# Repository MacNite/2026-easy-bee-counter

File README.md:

# Bee Counter Redesign — Full Specification
### Single PCB + 3D Printed Housing, reported over BLE to HiveHub

A redesign of the [2019-easy-bee-counter](https://github.com/hydronics2/2019-easy-bee-counter)
by hydronics2: 24 entrance gates, 48 reflective IR sensors read through I²C
port expanders, and an always-on ESP32-C6 doing the counting and reporting
totals over BLE.

> **Status:** the PCB (`PCB_files/easy-bee-counter-2026.kicad_*`) and the
> ESP32-C6 firmware (`Firmware/`) are implemented. The 3D-printed housing
> (Section 5) is the remaining mechanical work.

---

## 1. System Overview

The **ESP32-C6 mini** runs always-on as a dedicated bee counter and advertises
as a connectable BLE peripheral. A HiveHub wakes roughly every 10 minutes,
connects, reads one JSON characteristic of lifetime totals and disconnects,
combining the counts with weight/timestamp data before logging and transmitting.

```
[HiveHub ESP32] ←——— BLE/GATT ———→ [ESP32-C6 mini]
  wakes every ~10 min                always-on, ~15 mA
  RTC, SD, WiFi, scale               bee counting, 3× MCP23017 (I²C)
```

The counter's own I²C bus (`Wire`, silk D4 = GPIO22 SDA / silk D5 = GPIO23 SCL) is used only to reach
the 3× MCP23017 port expanders.

> **The wired HiveScale link is gone.** Earlier revisions ran the C6's second
> I²C controller as a permanent slave at 0x30, serving a register map to a
> HiveScale polling over J1 — and the firmware for it has been removed, because
> HiveHub reads counters over BLE only and dropped its wired client. Sections
> below still describe the J1 connector and its cable, since both are physically
> on the PCB; no firmware brings that bus up, so populating them is optional.

---

## 2. Complete Bill of Materials

### 2.1 Microcontroller

| # | Component | Qty | Notes |
|---|-----------|-----|-------|
| 1 | Seeed XIAO ESP32C6 (Seeed 113991054) | 1 | Always-on bee counter MCU. ~15 mA active, 3.3 V logic, USB-C. Two hardware I²C controllers. **Silk D0..D10 ≠ GPIO numbers** — see `Firmware/include/pins.h` |

### 2.2 I/O Expansion (replaces all 6× 74HC165)

| # | Component | Qty | Notes |
|---|-----------|-----|-------|
| 2 | MCP23017-E/SP (DIP-28) | 3 | 16 inputs each = 48 total. I²C addresses 0x20, 0x21, 0x22 (on bus 0) |

### 2.3 IR Sensors

| # | Component | Qty | Notes |
|---|-----------|-----|-------|
| 3 | QRE1113 or ITR8307 reflectance sensor | 48 | 2 per gate × 24 gates. ITR8307 from LCSC is cheaper (~€0.13 each) |

### 2.4 MOSFETs (IR LED switching)

| # | Component | Qty | Notes |
|---|-----------|-----|-------|
| 4 | IRLB8721PbF N-channel MOSFET (TO-220) | 3 | 3.3 V gate-safe. One per MCP23017: Q1 = LED_BANK_1 (gates 00..07), Q2 = LED_BANK_2 (gates 10..17), Q3 = LED_BANK_3 (gates 20..27). Individually switchable at runtime — see [Power Budget](#6-power-budget) |

### 2.5 Resistors

| # | Component | Qty | Notes |
|---|-----------|-----|-------|
| 5 | 22 Ω bussed SIP resistor (9-pin, 8R) | 3 | IR LED current limiting (2 LEDs in series per gate) |
| 6 | 100 kΩ bussed SIP resistor (9-pin, 8R) | 6 | Sensor pull-up resistors (1 per MCP23017 input, to +3.3 V) |
| 7 | 10 kΩ resistor (through-hole) | 6 | MOSFET gate pull-downs (3×), MCP23017 RESET pull-ups (3×) |
| 8 | 4.7 kΩ resistor (through-hole) | 2 | Bus 0 I²C pull-ups (SDA + SCL to 3.3 V), R4/R5 |

> J1 (the retired HiveScale link) does **not** need on-board pull-ups — those were
> provided by the HiveScale-side I²C network.

### 2.6 Capacitors

| # | Component | Qty | Notes |
|---|-----------|-----|-------|
| 9 | 100 nF ceramic capacitor (through-hole) | 6 | Decoupling, 1 per MCP23017 VDD pin + 3 spare |
| 10 | 10 µF electrolytic capacitor | 1 | Bulk decoupling on 3.3 V rail |

### 2.7 Connectors

| # | Component | Qty | Notes |
|---|-----------|-----|-------|
| 11 | 4-pin JST-PH or screw terminal (I²C bus 1 + GND + 3.3 V) | 1 | Connection cable to HiveScale (J1) |
| 12 | 2-pin screw terminal | 1 | 3.3 V power input from HiveScale |
| 13 | USB-C connector (on C6 mini board) | — | For firmware flashing / serial only |

### 2.8 PCB & Housing

| # | Component | Qty | Notes |
|---|-----------|-----|-------|
| 14 | Custom PCB (single board, black substrate) | 1 | Designed in KiCad (`PCB_files/`). Order black. See Section 4 |
| 15 | 3D printed top baffle / housing | 1 | Carbon-filled PETG or ASA. See Section 5 |
| 16 | M2×6 screws | 8 | PCB to housing standoffs |
| 17 | M2 brass heat-set inserts | 8 | Into 3D printed housing |

---

## 3. Wiring & Connection Map

### 3.1 I²C Buses

This board uses **two separate I²C buses**, one per controller:

**Bus 0 (`Wire`) — MCP23017 master bus.** Silk D4 = GPIO22 = SDA, silk D5 = GPIO23 = SCL. On-board
4.7 kΩ pull-ups (R4/R5) to 3.3 V.

```
XIAO D4 = GPIO22 (SDA) ——+——————+——————+——— 4.7 kΩ ——→ 3.3 V
                        |      |      |
                      MCP1   MCP2   MCP3
                      0x20   0x21   0x22

XIAO D5 = GPIO23 (SCL) ——+——————+——————+——— 4.7 kΩ ——→ 3.3 V
```

**J1 (silk D2 / D3 = GPIO2 / GPIO21) — the retired HiveScale slave bus.** The pads and traces
are on the board, and pull-ups were supplied by the HiveScale side. **No current
firmware brings this controller up**, so the pins stay inputs and populating J1
is optional — see the note in Section 1.

> **Note on the schematic net names:** the schematic labels the master bus nets
> "/SDA" and "/SDC" (a typo for SCL), and the LED-bank nets "/GPIO4" / "/GPIO5"
> / "/GPIO6". Those are just net *names* — physically the LED banks are driven
> from silk D8 = GPIO19, D9 = GPIO20 and D10 = GPIO18. U5 is a Seeed XIAO ESP32C6, whose silk
> numbers are **not** its GPIO numbers; see `Firmware/include/pins.h` for the
> authoritative map.

### 3.2 MCP23017 Wiring (repeat for each of the 3 chips, all on bus 0)

| MCP23017 Pin | Connection | Notes |
|---|---|---|
| 9 (VDD) | 3.3 V | Add 100 nF ceramic cap to GND nearby |
| 10 (VSS) | GND | |
| 12 (SCL) | Bus 0 SCL (silk D5 = GPIO23) | |
| 13 (SDA) | Bus 0 SDA (silk D4 = GPIO22) | |
| 15 (A0) | GND / 3.3 V | Address bit 0 (see table below) |
| 16 (A1) | GND / 3.3 V | Address bit 1 |
| 17 (A2) | GND / 3.3 V | Address bit 2 |
| 18 (RESET) | 3.3 V via 10 kΩ | Tie high; no active reset needed |
| 21–28 (GPA0–7) | IR sensor outputs (inner sensors) | 8 sensors per chip |
| 1–8 (GPB0–7) | IR sensor outputs (outer sensors) | 8 sensors per chip |

**Address configuration:**

| Chip | I²C Address | A2 | A1 | A0 | Gates |
|------|-------------|----|----|----|----|
| MCP1 (U2) | 0x20 | GND | GND | GND | 00–07 |
| MCP2 (U3) | 0x21 | GND | GND | 3.3 V | 10–17 |
| MCP3 (U4) | 0x22 | GND | 3.3 V | GND | 20–27 |

> Gate tags have gaps (08, 09, 18, 19, 28, 29 are skipped) to keep the
> per-chip pin→gate map clean; there are 24 physical gates indexed 0..23
> internally.

### 3.3 IR Sensor Wiring (per sensor pair, 24× repeated)

Each gate has 2 sensors — one "inner" (towards hive), one "outer" (towards field).

```
QRE1113 pin 1 (Anode / LED+)   ——→ LED string common (+ / 3.3 V via 22 Ω)
QRE1113 pin 2 (Cathode / LED-) ——→ MOSFET Drain (bank rail)
QRE1113 pin 3 (Collector)      ——→ MCP23017 GPIO input pin + 100 kΩ pull-up to 3.3 V
QRE1113 pin 4 (Emitter)        ——→ GND
```

Logical convention in firmware: **sensor reads LOW = beam reflected/blocked
(bee in beam); HIGH = clear or LEDs off.**

### 3.4 MOSFET Wiring (IRLB8721PbF, 3× identical — one per MCP23017)

| IRLB8721 Pin | Connection |
|---|---|
| Gate (pin 1) | Bank enable GPIO from the table below, + 10 kΩ pull-down to GND |
| Drain (pin 2) | IR LED cathode strings for that bank |
| Source (pin 3) | GND |

| FET | Bank | Gates | XIAO silk | GPIO | Schematic net |
|---|---|---|---|---|---|
| Q1 | LED_BANK_1 | 00..07 (U2 @ 0x20) | D8  | GPIO19 | /GPIO4 |
| Q2 | LED_BANK_2 | 10..17 (U3 @ 0x21) | D9  | GPIO20 | /GPIO5 |
| Q3 | LED_BANK_3 | 20..27 (U4 @ 0x22) | D10 | GPIO18 | /GPIO6 |

Driving the gate HIGH turns that bank's IR emitters ON.

### 3.5 HiveScale I²C Connection Cable (bus 1, connector J1)

4-wire cable between HiveScale and bee counter PCB:

| Wire | Signal |
|---|---|
| Red | 3.3 V (from HiveScale to power the C6 + MCP23017s) |
| Black | GND |
| Yellow | SDA (silk D2 = GPIO2) |
| Blue | SCL (silk D3 = GPIO21) |

This cable served the retired wired link and is not needed for a BLE counter;
the board only needs 3.3 V and GND. The MCP23017s live on their own bus and were
never visible over J1 in any case.

---

## 4. PCB Dimensions & Layout

### 4.1 Target Dimensions

Based on standard Langstroth 10-frame hive (476 mm internal entrance width):

| Dimension | Value | Notes |
|---|---|---|
| PCB length | 375 mm | Covers full entrance, leaving margin each side for housing walls |
| PCB width | 40 mm | Enough for components + connector |
| Gate pitch | 15.6 mm | 375 mm / 24 gates. Each gate ~12 mm clear opening + 3.6 mm divider wall |
| Sensor pair spacing | 8 mm | Inner-to-outer sensor distance within one gate |

**Note for European Zander/Deutsch Normal hives:** entrance width is typically 370 mm — adjust PCB length accordingly.

### 4.2 Component Placement

```
[USB-C]  [C6 mini]  [MCP1]  [MCP2]  [MCP3]  [J1 I²C connector]
                    ← electronics zone, left end →

← 24 sensor pairs spread across the remaining length →

Top edge: inner sensors (facing hive interior)
Bottom edge: outer sensors (facing landing board)
```

- ESP32-C6 and MCP23017s cluster at the left end of the PCB
- Sensor pairs run along the full length
- Q1/Q2 MOSFETs near the sensor zone centre with thermal via to bottom copper pour
- Keep the MCP I²C traces short; keep the J1 routing away from the MCP bus
- 100 nF decoupling caps placed directly adjacent to each MCP23017 VDD pin

---

## 5. 3D Printed Housing Specification

### 5.1 Material

| Property | Requirement |
|---|---|
| Material | Carbon-filled PETG (e.g. Prusament PETG CF) or ASA |
| Color | Black (carbon content ensures genuine IR opacity at 950 nm) |
| Layer height | 0.2 mm or finer for gate walls |
| Infill | 40%+ for structural rigidity |

Do NOT use standard black PLA or standard black PETG — most black dyes are IR-transparent at 950 nm. Carbon-filled variants are the exception.

### 5.2 Housing Parts

**Part 1 — Bottom tray** (holds PCB):
- Internal width: PCB width + 2 mm clearance
- Internal length: PCB length + 2 mm clearance
- Depth: 12 mm (enough for tallest through-hole component)
- 4 M2 standoff bosses at corners, 3 mm proud of floor
- Cable exit slot at left end for I²C cable

**Part 2 — Top baffle** (replaces the original second PCB):
- Same footprint as bottom tray
- 24 channel slots cut through, matching sensor pair positions
- Channel slot width: 12 mm (bee passage width)
- Channel slot height (depth of baffle): 10 mm
- Divider wall thickness between channels: 3.6 mm
- Snap or M2 screw attachment to bottom tray (4 points)
- Landing ramp angle on outer face: 15° downward slope toward hive entrance

### 5.3 Gate Geometry

```
Top view of one gate channel:
┌────────────────────────┐
│  ←── 12 mm ──→         │  ← bee passage
│  [outer sensor]         │  ← facing landing board
│          ↕ 8 mm         │
│  [inner sensor]         │  ← facing hive
└────────────────────────┘
     ← 3.6 mm wall →
```

Sensors face upward from the bottom PCB into the channel. The black baffle absorbs any IR not reflected by a bee.

---

## 6. Power Budget

| Component | Current | Count | Total |
|---|---|---|---|
| ESP32-C6 mini (active, BLE advertising) | 15 mA | 1 | 15 mA |
| MCP23017 (active) | 1 mA | 3 | 3 mA |
| Quiescent leakage | — | — | ~1 mA |
| **Electronics subtotal** | | | **~19 mA** |
| IR emitters, all banks lit (peak) | ~20–40 mA/gate | 24 gates | **~0.5–1.0 A** |
| IR emitters, pulsed at 35 % duty (average) | | | **~170–350 mA** |
| HiveScale ESP32 (sleep) | ~0.05 mA | 1 | 0.05 mA |
| HiveScale ESP32 (awake, ~10 min cycle) | 80 mA × 30 s / 600 s | 1 | ~4 mA avg |

**The emitters are the power budget.** Each gate drives two IR LEDs in series
through a 22 Ω ballast off the 3.3 V rail — roughly (3.3 − 2·V_f)/22, i.e. tens
of milliamps per gate — and the pulsed sampler lights all three banks together
for the settle+read window of every 5 ms poll. Everything else on the board
together is under 20 mA, an order of magnitude below. The per-gate figure
depends on the actual LED forward voltage; **measure it on an assembled board**
before sizing a panel or a pack, rather than trusting the range above.

Three things follow, and all three are implemented:

* **Pulsed emitters** (`LedMode::AUTO`, the default since the 2026-06 revision)
  cut the duty cycle from 100 % to ~35 %. Raising `POLL_INTERVAL_MS` lowers it
  proportionally. There is no `CMD_LEDS_OFF` — that was an I²C command on the
  wired link, which no longer exists; the bench overrides are the `-DIR_DEBUG`
  console's `1`/`0`/`a` keys.
* **Night mode** parks the emitters entirely through the hours honey bees do not
  fly, on request from HiveHub. Over an 8–12 h night that is the difference
  between the counter fitting an off-grid budget and not. See
  [`docs/ble-mode.md`](docs/ble-mode.md#night-mode-the-control-characteristic) —
  including why it is *not* implemented as deep sleep.
* **Per-bank enables** switch the three MOSFETs individually, so an entrance
  narrower than 24 gates costs only the banks it uses. Measured on an assembled
  board, at 3.3 V:

  | Banks enabled | Gates counted | Draw |
  |---|---|---|
  | 1 | 8 | ~0.14 A |
  | 2 | 16 | ~0.22 A |
  | 3 (default) | 24 | ~0.30 A |

  Roughly 80 mA per bank on top of a ~60 mA floor. All three are enabled unless
  HiveHub says otherwise (three checkboxes per device in its dashboard), and a
  counter that resets comes back with all three on. It composes with night mode
  rather than competing with it. See
  [`docs/ble-mode.md`](docs/ble-mode.md#emitter-banks-the-other-power-control).

Add solar for indefinite runtime.

---

## 7. BLE Data Handoff

The counter is a connectable BLE peripheral. The canonical definition of the
GATT contract lives in [`docs/ble-mode.md`](docs/ble-mode.md); this is a summary.

- Advertises as `HiveTraffic-AB:12` — the product name suffixed with the last
  two bytes of the counter's own BLE address, so several counters in range are
  distinct rows in a scan list. HiveHub connects by the MAC paired in its
  portal and never matches on the name.
- One service, `8e8b0101-7a1c-4b9e-9a2f-1d6e0b9c1a01`, holding a READ
  measurement characteristic, a READ/WRITE control characteristic (night mode
  and emitter-bank enables) and three OTA characteristics.
- The measurement value is built on read, so it is never a stale snapshot:

```json
{"fw":4,"ver":"0.2.0","uptime_s":1234,"status":15,"num_gates":24,
 "mcps_healthy":3,"total_in":100,"total_out":95,"glitches":2,"idle_s":0}
```

`mcps_healthy` counts MCP23017 port expanders (0..3), not gates — each covers
eight of the 24. `idle_s` is the night-mode countdown, `0` while counting. `fw`
is the wire format's revision, not the image version (`ver`); see
[docs/ble-mode.md](docs/ble-mode.md) for the revision history and the deployment
order it requires.

### Totals only

`total_in` / `total_out` are monotonic lifetime counters; HiveHub differences
consecutive reads into per-interval counts on its server. Nothing on the device
is consumed by being read, so a missed connection cannot lose traffic.

This replaced a register map with interval counters that a `CMD_LATCH` command
zeroed — where a HiveScale that read but failed to latch, or latched but failed
to read, silently lost an interval.

### OTA over BLE

HiveHub relays a new C6 image (downloaded over WiFi) into the counter's OTA
characteristics: BEGIN (size + CRC-32) → DATA frames → END (verify, swap slots,
reboot). Gate counting pauses for the duration. See
[`docs/ble-mode.md`](docs/ble-mode.md).

---

## 8. Firmware Summary

Implemented in `Firmware/` (PlatformIO, `seeed_xiao_esp32c6` env). See
`Firmware/README.md` for build/flash and tuning details.

### ESP32-C6 (bee counter)
- **`Wire` (master):** continuously polls the 3× MCP23017 (~5 ms loop), reading
  all 16 inputs per chip. Read failures are detected, so an expander that goes
  missing has its gates skipped rather than read as "all beams blocked", and is
  re-probed until it comes back.
- **BLE/GATT peripheral:** serves lifetime totals as JSON on read, accepts a
  firmware image on the OTA characteristics, and takes a bounded "stop sensing"
  request plus an emitter-bank enable mask on the control characteristic
  (`src/ble_link.cpp`).
- Per-gate debounce + direction state machine (IDLE → INNER/OUTER_FIRST →
  PAIRED) emits IN/OUT counts; glitches tallied for diagnostics. The logic lives
  in `Firmware/include/gate_logic.h` and is covered by host-side tests
  (`Firmware/test/run_tests.sh`).
- IR banks driven on GPIO19 / silk D8 (bank 1), GPIO20 / silk D9 (bank 2) and
  GPIO18 / silk D10 (bank 3) — one MOSFET per MCP23017. LED mode and per-bank
  enables are both settable from the IR_DEBUG serial console (`1`/`0`/`a` and
  `4`/`5`/`6`), and the bank mask is settable over BLE by HiveHub.
- BLE OTA image receiver (`Update` library) with size + CRC-32 verification
  before the inactive app slot is selected.

### HiveHub ESP32 (data aggregator — lives in the HiveHub firmware, not here)
- On wake: read RTC timestamp, read weight, connect to the counter over BLE and
  read its lifetime totals.
- Difference consecutive totals server-side to get the interval counts.
- Write combined record to SD card; transmit via WiFi if available.
- Optionally relay a firmware update to the C6 over BLE (`update_beecounter`).
- Optionally re-arm the counter's night-mode suspension for the next cycle, and
  re-assert its emitter-bank enable mask.
- Sleep ~10 minutes.

---

## 9. Key Datasheet References

| Component | Key parameter |
|---|---|
| IRLB8721PbF | Vgs(th) max 2.4 V — fully on at 3.3 V ✓ |
| MCP23017 | 3× address pins → up to 8 devices on one bus; 1.7 MHz I²C |
| QRE1113 | 950 nm IR, 20 mA forward current, reflective mode |
| ESP32-C6 | **Two** independent I²C controllers; GPIO map is board-specific (see `pins.h`) |
| DS3231 | ±2 ppm accuracy, integrated TCXO, I²C, backup battery (on HiveScale) |

---

*Document version 2.0 — based on the 2019-easy-bee-counter project by
hydronics2, redesigned for MCP23017 I²C, ESP32-C6 mini, dual independent I²C
buses, OTA-over-I²C, dual-hive addressing, single PCB + 3D printed housing, and
HiveScale integration.*

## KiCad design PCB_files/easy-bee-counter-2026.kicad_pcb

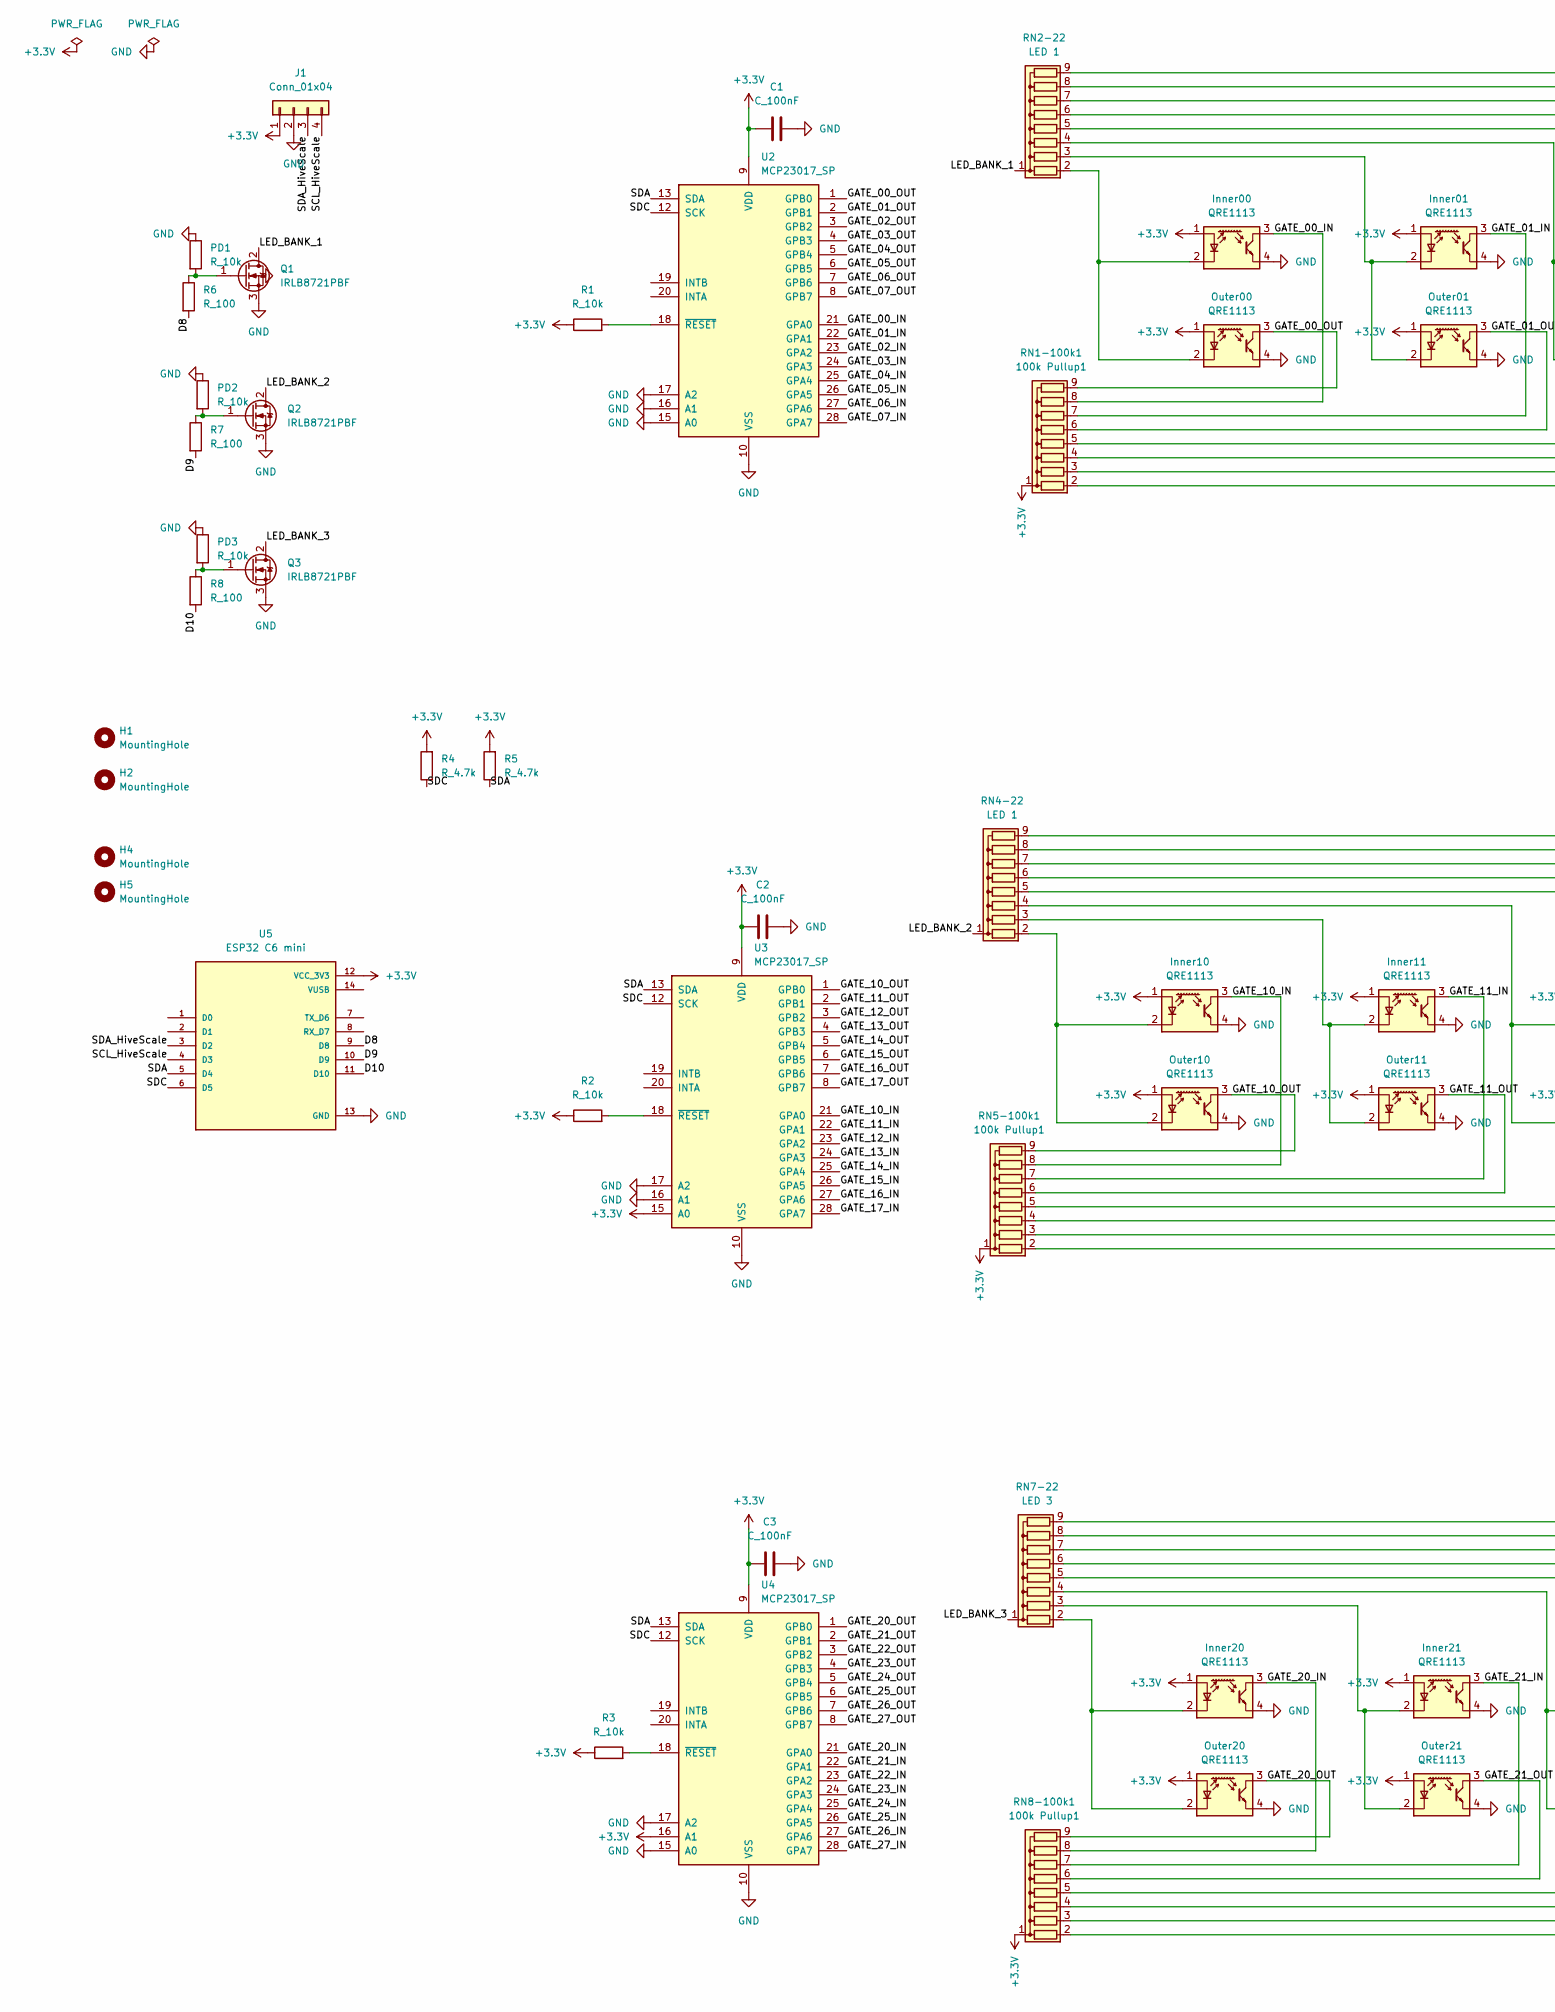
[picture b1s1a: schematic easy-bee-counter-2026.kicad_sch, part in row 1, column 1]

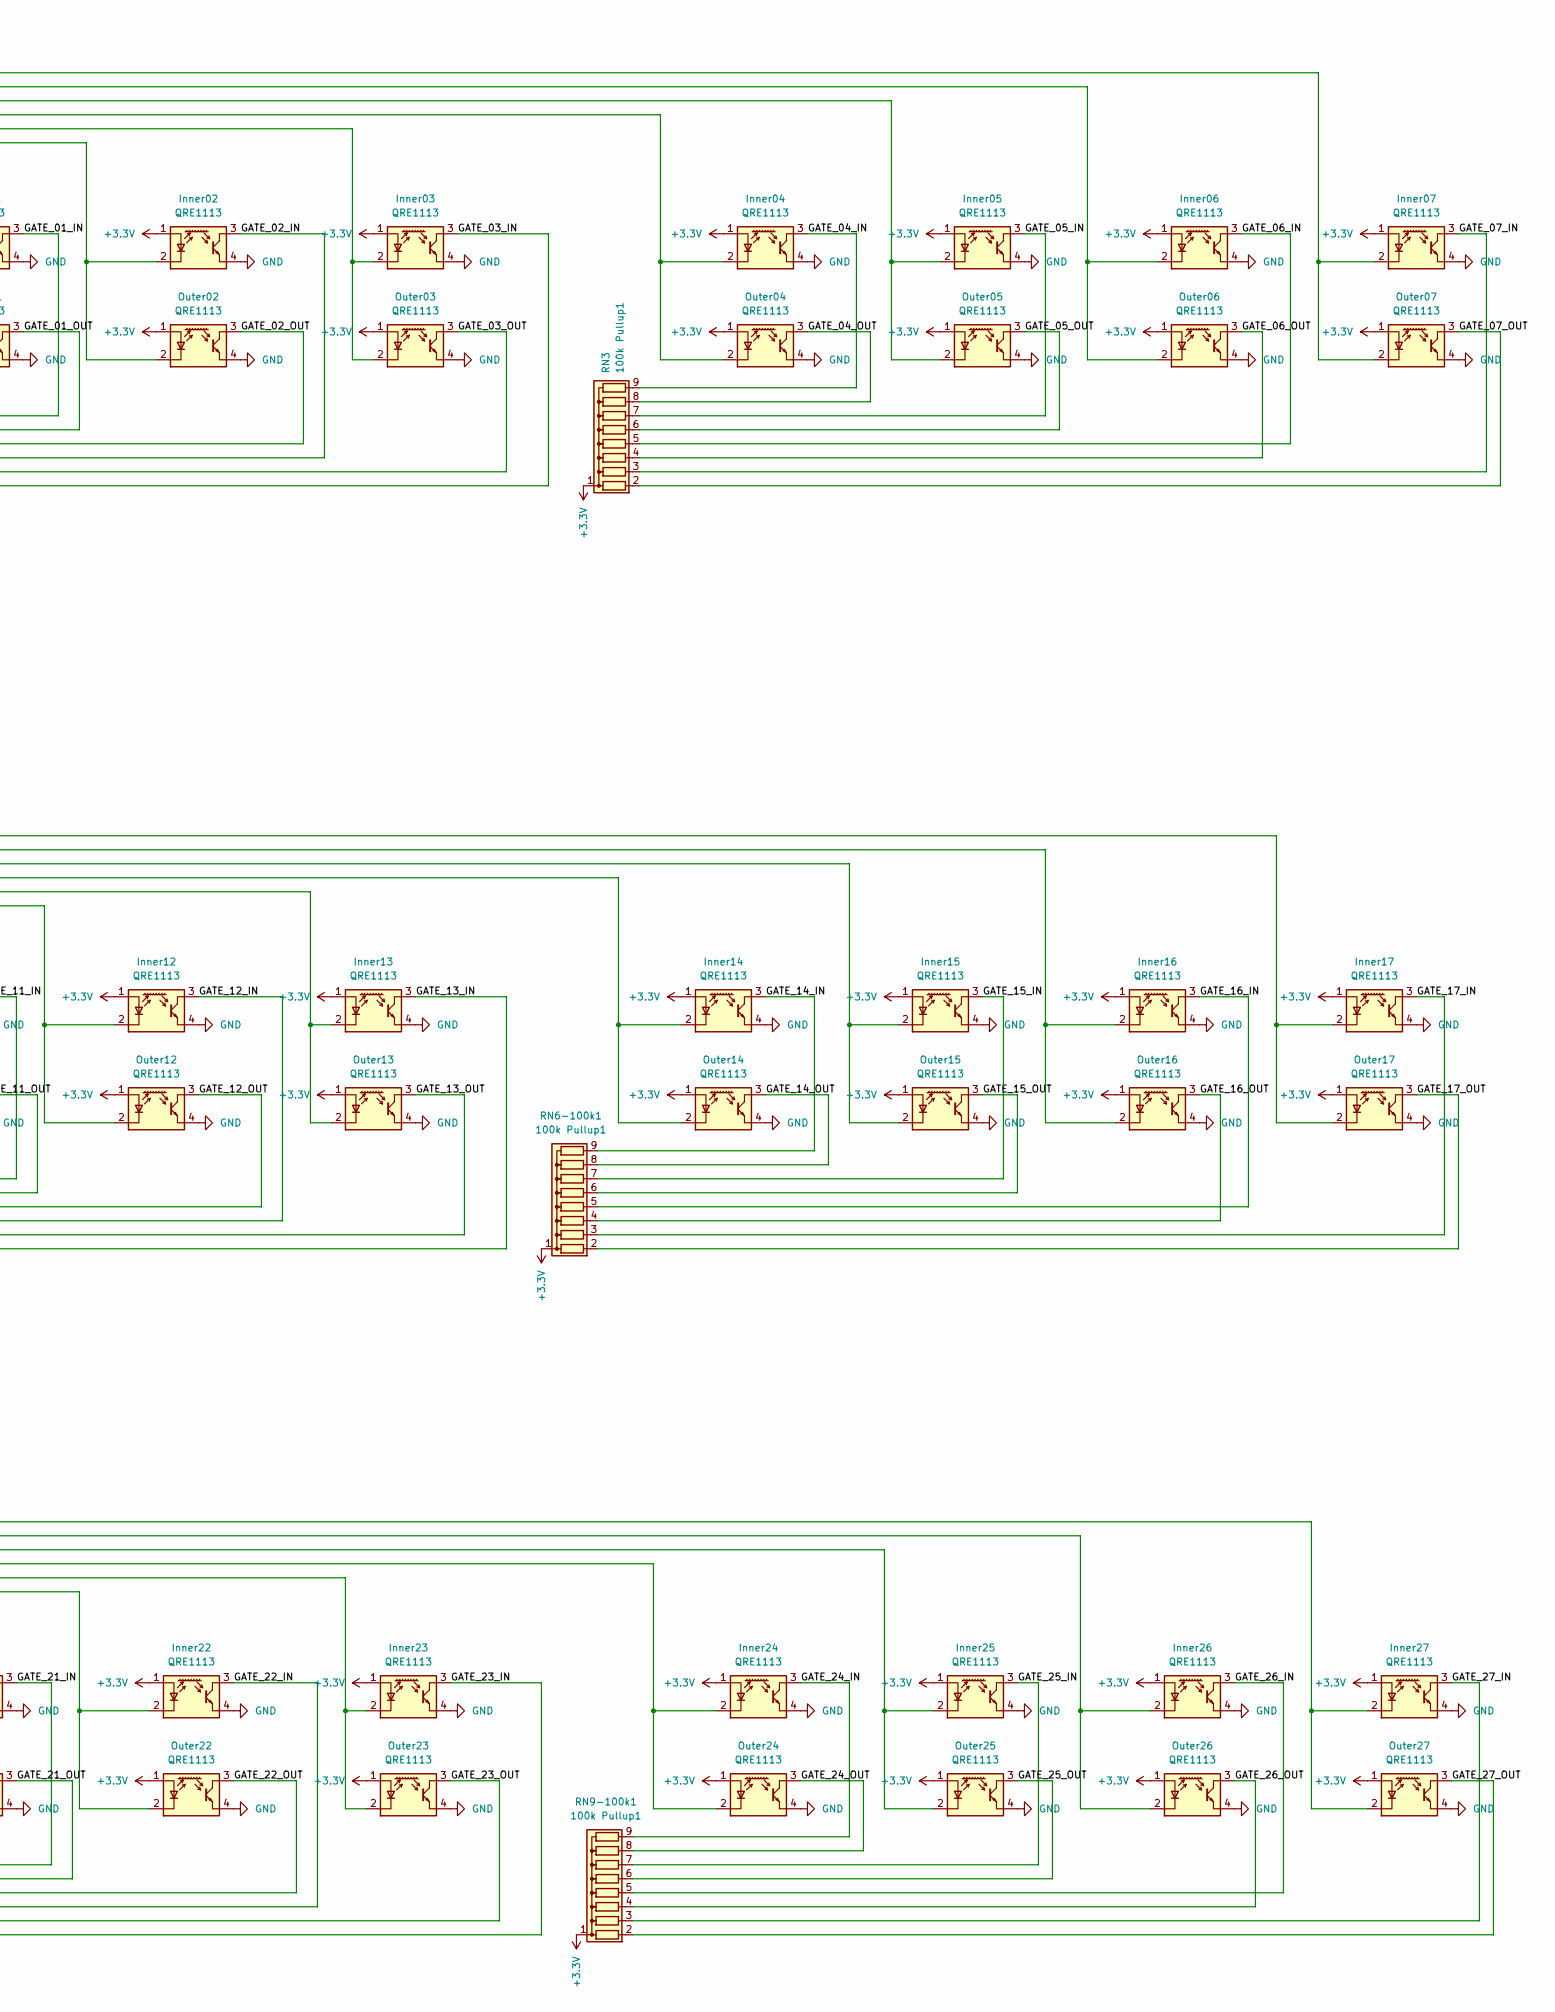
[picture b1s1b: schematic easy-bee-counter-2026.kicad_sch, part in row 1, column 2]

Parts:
C1, C2, C3: C_100nF; C_Disc_D5.0mm_W2.5mm_P5.00mm
H1, H2, H4, H5: MountingHole; MountingHole_3.2mm_M3
Inner00, Inner01, Inner02, Inner03, Inner04, Inner05, Inner06, Inner07, Inner10, Inner11, Inner12, Inner13, Inner14, Inner15, Inner16, Inner17, Inner20, Inner21, Inner22, Inner23, Inner24, Inner25, Inner26, Inner27: QRE1113; OnSemi_CASE100AQ
J1: Conn_01x04; TerminalBlock_Xinya_XY308-2.54-4P_1x04_P2.54mm_Horizontal
Outer00, Outer01, Outer02, Outer03, Outer04, Outer05, Outer06, Outer07, Outer10, Outer11, Outer12, Outer13, Outer14, Outer15, Outer16, Outer17, Outer20, Outer21, Outer22, Outer23, Outer24, Outer25, Outer26, Outer27: QRE1113; OnSemi_CASE100AQ
PD1, PD2, PD3: R_10k; R_Axial_DIN0207_L6.3mm_D2.5mm_P7.62mm_Horizontal
Q1, Q2, Q3: IRLB8721PBF; TO-220-3_Vertical
R1, R2, R3: R_10k; R_Axial_DIN0207_L6.3mm_D2.5mm_P7.62mm_Horizontal
R4, R5: R_4.7k; R_Axial_DIN0207_L6.3mm_D2.5mm_P7.62mm_Horizontal
R6, R7, R8: R_100; R_Axial_DIN0207_L6.3mm_D2.5mm_P7.62mm_Horizontal
RN1-100k1, RN3, RN5-100k1, RN6-100k1, RN8-100k1, RN9-100k1: 100k Pullup1; R_Array_SIP9
RN2-22, RN4-22: LED 1; R_Array_SIP9
RN7-22: LED 3; R_Array_SIP9
U2, U3, U4: MCP23017_SP; DIP-28_W7.62mm
U5: ESP32 C6 mini; MODULE_113991054; PARTREV 23/05/2022

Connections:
+3.3V: C1.1, C2.1, C3.1, Inner00.1 (A), Inner01.1 (A), Inner02.1 (A), Inner03.1 (A), Inner04.1 (A), Inner05.1 (A), Inner06.1 (A), Inner07.1 (A), Inner10.1 (A), Inner11.1 (A), Inner12.1 (A), Inner13.1 (A), Inner14.1 (A), Inner15.1 (A), Inner16.1 (A), Inner17.1 (A), Inner20.1 (A), Inner21.1 (A), Inner22.1 (A), Inner23.1 (A), Inner24.1 (A), Inner25.1 (A), Inner26.1 (A), Inner27.1 (A), J1.1, Outer00.1 (A), Outer01.1 (A), Outer02.1 (A), Outer03.1 (A), Outer04.1 (A), Outer05.1 (A), Outer06.1 (A), Outer07.1 (A), Outer10.1 (A), Outer11.1 (A), Outer12.1 (A), Outer13.1 (A), Outer14.1 (A), Outer15.1 (A), Outer16.1 (A), Outer17.1 (A), Outer20.1 (A), Outer21.1 (A), Outer22.1 (A), Outer23.1 (A), Outer24.1 (A), Outer25.1 (A), Outer26.1 (A), Outer27.1 (A), R1.1, R2.1, R3.1, R4.2, R5.2, RN1-100k1.1 (common), RN3.1 (common), RN5-100k1.1 (common), RN6-100k1.1 (common), RN8-100k1.1 (common), RN9-100k1.1 (common), U2.9 (VDD), U3.9 (VDD), U3.15 (A0), U4.9 (VDD), U4.16 (A1), U5.12 (VCC_3V3)
/D8: R6.2, U5.9 (D8)
/D9: R7.2, U5.10 (D9)
/D10: R8.2, U5.11 (D10)
/GATE_00_IN: Inner00.3, RN1-100k1.8 (R7), U2.21 (GPA0)
/GATE_00_OUT: Outer00.3, RN1-100k1.9 (R8), U2.1 (GPB0)
/GATE_01_IN: Inner01.3, RN1-100k1.7 (R6), U2.22 (GPA1)
/GATE_01_OUT: Outer01.3, RN1-100k1.6 (R5), U2.2 (GPB1)
/GATE_02_IN: Inner02.3, RN1-100k1.4 (R3), U2.23 (GPA2)
/GATE_02_OUT: Outer02.3, RN1-100k1.5 (R4), U2.3 (GPB2)
/GATE_03_IN: Inner03.3, RN1-100k1.2 (R1), U2.24 (GPA3)
/GATE_03_OUT: Outer03.3, RN1-100k1.3 (R2), U2.4 (GPB3)
/GATE_04_IN: Inner04.3, RN3.9 (R8), U2.25 (GPA4)
/GATE_04_OUT: Outer04.3, RN3.8 (R7), U2.5 (GPB4)
/GATE_05_IN: Inner05.3, RN3.7 (R6), U2.26 (GPA5)
/GATE_05_OUT: Outer05.3, RN3.6 (R5), U2.6 (GPB5)
/GATE_06_IN: Inner06.3, RN3.5 (R4), U2.27 (GPA6)
/GATE_06_OUT: Outer06.3, RN3.4 (R3), U2.7 (GPB6)
/GATE_07_IN: Inner07.3, RN3.3 (R2), U2.28 (GPA7)
/GATE_07_OUT: Outer07.3, RN3.2 (R1), U2.8 (GPB7)
/GATE_10_IN: Inner10.3, RN5-100k1.8 (R7), U3.21 (GPA0)
/GATE_10_OUT: Outer10.3, RN5-100k1.9 (R8), U3.1 (GPB0)
/GATE_11_IN: Inner11.3, RN5-100k1.7 (R6), U3.22 (GPA1)
/GATE_11_OUT: Outer11.3, RN5-100k1.6 (R5), U3.2 (GPB1)
/GATE_12_IN: Inner12.3, RN5-100k1.4 (R3), U3.23 (GPA2)
/GATE_12_OUT: Outer12.3, RN5-100k1.5 (R4), U3.3 (GPB2)
/GATE_13_IN: Inner13.3, RN5-100k1.2 (R1), U3.24 (GPA3)
/GATE_13_OUT: Outer13.3, RN5-100k1.3 (R2), U3.4 (GPB3)
/GATE_14_IN: Inner14.3, RN6-100k1.9 (R8), U3.25 (GPA4)
/GATE_14_OUT: Outer14.3, RN6-100k1.8 (R7), U3.5 (GPB4)
/GATE_15_IN: Inner15.3, RN6-100k1.7 (R6), U3.26 (GPA5)
/GATE_15_OUT: Outer15.3, RN6-100k1.6 (R5), U3.6 (GPB5)
/GATE_16_IN: Inner16.3, RN6-100k1.5 (R4), U3.27 (GPA6)
/GATE_16_OUT: Outer16.3, RN6-100k1.4 (R3), U3.7 (GPB6)
/GATE_17_IN: Inner17.3, RN6-100k1.3 (R2), U3.28 (GPA7)
/GATE_17_OUT: Outer17.3, RN6-100k1.2 (R1), U3.8 (GPB7)
/GATE_20_IN: Inner20.3, RN8-100k1.8 (R7), U4.21 (GPA0)
/GATE_20_OUT: Outer20.3, RN8-100k1.9 (R8), U4.1 (GPB0)
/GATE_21_IN: Inner21.3, RN8-100k1.7 (R6), U4.22 (GPA1)
/GATE_21_OUT: Outer21.3, RN8-100k1.6 (R5), U4.2 (GPB1)
/GATE_22_IN: Inner22.3, RN8-100k1.4 (R3), U4.23 (GPA2)
/GATE_22_OUT: Outer22.3, RN8-100k1.5 (R4), U4.3 (GPB2)
/GATE_23_IN: Inner23.3, RN8-100k1.2 (R1), U4.24 (GPA3)
/GATE_23_OUT: Outer23.3, RN8-100k1.3 (R2), U4.4 (GPB3)
/GATE_24_IN: Inner24.3, RN9-100k1.9 (R8), U4.25 (GPA4)
/GATE_24_OUT: Outer24.3, RN9-100k1.8 (R7), U4.5 (GPB4)
/GATE_25_IN: Inner25.3, RN9-100k1.7 (R6), U4.26 (GPA5)
/GATE_25_OUT: Outer25.3, RN9-100k1.6 (R5), U4.6 (GPB5)
/GATE_26_IN: Inner26.3, RN9-100k1.5 (R4), U4.27 (GPA6)
/GATE_26_OUT: Outer26.3, RN9-100k1.4 (R3), U4.7 (GPB6)
/GATE_27_IN: Inner27.3, RN9-100k1.3 (R2), U4.28 (GPA7)
/GATE_27_OUT: Outer27.3, RN9-100k1.2 (R1), U4.8 (GPB7)
/LED_BANK_1: Q1.2 (D), RN2-22.1 (common)
/LED_BANK_2: Q2.2 (D), RN4-22.1 (common)
/LED_BANK_3: Q3.2 (D), RN7-22.1 (common)
/SCL_HiveScale: J1.4, U5.4 (D3)
/SDA: R5.1, U2.13 (SDA), U3.13 (SDA), U4.13 (SDA), U5.5 (D4)
/SDA_HiveScale: J1.3, U5.3 (D2)
/SDC: R4.1, U2.12 (SCK), U3.12 (SCK), U4.12 (SCK), U5.6 (D5)
GND: C1.2, C2.2, C3.2, Inner00.4, Inner01.4, Inner02.4, Inner03.4, Inner04.4, Inner05.4, Inner06.4, Inner07.4, Inner10.4, Inner11.4, Inner12.4, Inner13.4, Inner14.4, Inner15.4, Inner16.4, Inner17.4, Inner20.4, Inner21.4, Inner22.4, Inner23.4, Inner24.4, Inner25.4, Inner26.4, Inner27.4, J1.2, Outer00.4, Outer01.4, Outer02.4, Outer03.4, Outer04.4, Outer05.4, Outer06.4, Outer07.4, Outer10.4, Outer11.4, Outer12.4, Outer13.4, Outer14.4, Outer15.4, Outer16.4, Outer17.4, Outer20.4, Outer21.4, Outer22.4, Outer23.4, Outer24.4, Outer25.4, Outer26.4, Outer27.4, PD1.1, PD2.1, PD3.1, Q1.3 (S), Q2.3 (S), Q3.3 (S), U2.10 (VSS), U2.15 (A0), U2.16 (A1), U2.17 (A2), U3.10 (VSS), U3.16 (A1), U3.17 (A2), U4.10 (VSS), U4.15 (A0), U4.17 (A2), U5.13 (GND)
unnamed: Inner00.2 (K), Outer00.2 (K), RN2-22.2 (R1)
unnamed: Inner01.2 (K), Outer01.2 (K), RN2-22.3 (R2)
unnamed: Inner02.2 (K), Outer02.2 (K), RN2-22.4 (R3)
unnamed: Inner03.2 (K), Outer03.2 (K), RN2-22.5 (R4)
unnamed: Inner04.2 (K), Outer04.2 (K), RN2-22.6 (R5)
unnamed: Inner05.2 (K), Outer05.2 (K), RN2-22.7 (R6)
unnamed: Inner06.2 (K), Outer06.2 (K), RN2-22.8 (R7)
unnamed: Inner07.2 (K), Outer07.2 (K), RN2-22.9 (R8)
unnamed: Inner10.2 (K), Outer10.2 (K), RN4-22.2 (R1)
unnamed: Inner11.2 (K), Outer11.2 (K), RN4-22.3 (R2)
unnamed: Inner12.2 (K), Outer12.2 (K), RN4-22.4 (R3)
unnamed: Inner13.2 (K), Outer13.2 (K), RN4-22.5 (R4)
unnamed: Inner14.2 (K), Outer14.2 (K), RN4-22.6 (R5)
unnamed: Inner15.2 (K), Outer15.2 (K), RN4-22.7 (R6)
unnamed: Inner16.2 (K), Outer16.2 (K), RN4-22.8 (R7)
unnamed: Inner17.2 (K), Outer17.2 (K), RN4-22.9 (R8)
unnamed: Inner20.2 (K), Outer20.2 (K), RN7-22.2 (R1)
unnamed: Inner21.2 (K), Outer21.2 (K), RN7-22.3 (R2)
unnamed: Inner22.2 (K), Outer22.2 (K), RN7-22.4 (R3)
unnamed: Inner23.2 (K), Outer23.2 (K), RN7-22.5 (R4)
unnamed: Inner24.2 (K), Outer24.2 (K), RN7-22.6 (R5)
unnamed: Inner25.2 (K), Outer25.2 (K), RN7-22.7 (R6)
unnamed: Inner26.2 (K), Outer26.2 (K), RN7-22.8 (R7)
unnamed: Inner27.2 (K), Outer27.2 (K), RN7-22.9 (R8)
unnamed: PD1.2, Q1.1 (G), R6.1
unnamed: PD2.2, Q2.1 (G), R7.1
unnamed: PD3.2, Q3.1 (G), R8.1
unnamed: R1.2, U2.18 (~RESET)
unnamed: R2.2, U3.18 (~RESET)
unnamed: R3.2, U4.18 (~RESET)

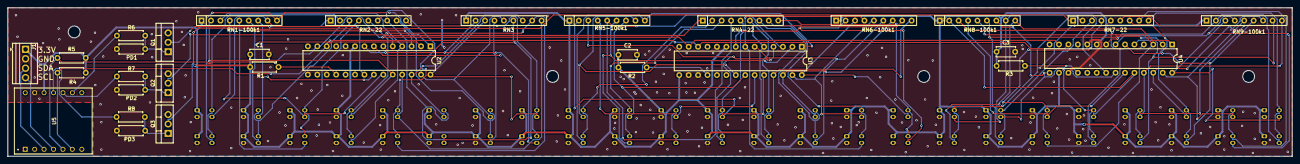
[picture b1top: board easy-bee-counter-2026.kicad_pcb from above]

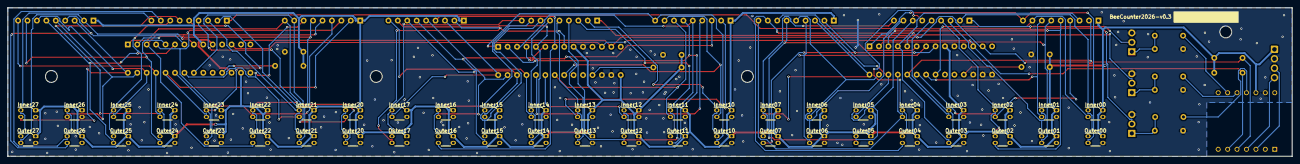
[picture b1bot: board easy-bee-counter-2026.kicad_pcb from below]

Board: 2 copper layers, 346.0 x 40.0 mm, 83 parts (48 on the bottom side), 90 nets.

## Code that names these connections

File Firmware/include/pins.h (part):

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//   ----   ----   ---------------------------------------------------------
//   D0  -> GPIO0
//   D1  -> GPIO1
//   D2  -> GPIO2   SDA_HiveScale (unused: the wired link was removed)
//   D3  -> GPIO21  SCL_HiveScale (unused: the wired link was removed)
//   D4  -> GPIO22  /SDA   (I2C data, MCP23017 master bus)
//   D5  -> GPIO23  /SDC   (I2C clock, schematic spells it "SDC")
//   D6  -> GPIO16  TX (UART0)                    [unused on this board]
//   D7  -> GPIO17  RX (UART0)                    [unused on this board]
//   D8  -> GPIO19  /GPIO4 net -> Q1 gate (LED_BANK_1 enable, gates 00..07)
//   D9  -> GPIO20  /GPIO5 net -> Q2 gate (LED_BANK_2 enable, gates 10..17)
//   D10 -> GPIO18  /GPIO6 net -> Q3 gate (LED_BANK_3 enable, gates 20..27)
//
// Two traps live in that table, and this firmware fell into both:
//
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
// Bus 0 (Wire) — master to the MCP23017s.
constexpr int I2C_SDA           = 22;   // U5 pin 5  / silk "D4" -> /SDA net
constexpr int I2C_SCL           = 23;   // U5 pin 6  / silk "D5" -> /SDC net

// One IRLB8721 per MCP23017 since the 2026-08 revision (was two FETs total).
constexpr int IR_LED_BANK_1_EN  = 19;   // U5 pin 9  / silk "D8"  -> Q1 gate -> gates 00..07
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
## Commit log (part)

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2026-05-13 Project Restructure
2026-05-13 Readme udpate
2026-05-13 updated gitignore
2026-05-27 Added first pcb-file-version
2026-05-27 Initial release of BeeCounter firmware with i2c
2026-05-27 Updated for dual hive setup
2026-05-27 Bugfix
2026-05-28 fixed 2nd i2c interface
2026-05-30 Added dual i2c and ota-firmware update
2026-06-02 Updated documentation
2026-06-12 added pulse led to firmware
2026-06-15 Add USB serial IR-sensor debug console for bench testing
    Adds an interactive, USB-only debug console gated behind a new -DIR_DEBUG
    build flag (esp32-c6-devkitc-1-irdebug env). It streams the raw inner/outer
    beam state of all 24 gates over USB CDC with no HiveScale/I2C master attached,
    and lets you force the IR LEDs on/off/auto from the serial monitor. The flag
    keeps all of this out of the production firmware.
2026-06-15 added debug mode
2026-06-15 Add I2C bus scanner ('i') to IR debug console
    Probes every 7-bit address on the master bus and reports what ACKs, to
    distinguish a wiring/pin fault from an MCP23017 address-strap fault during
    bench bring-up.
2026-06-15 debug_pins_update
2026-06-16 revised pcb design
2026-06-18 fixed ota updates
